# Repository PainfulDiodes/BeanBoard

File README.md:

# BeanBoard

QWERTY Keyboard, simple LCD display and GPIO for [BeanZee](https://github.com/PainfulDiodes/BeanZee)

# Design

## Keyboard  
Aiming for the simplest possible design, using a simple matrix of switches. 

Diodes are used with each switch to prevent [ghosting](https://en.wikipedia.org/wiki/Key_rollover#Key_jamming_and_ghosting).  

The circuit expects the CPU to send a "strobe" to a keyboard output port. A latch is used to capture the strobe - so that the state persists after the CPU has stopped outputting to the port. This strobe should have only one bit set high. This is the "live" row.

Then the CPU will read from a keyboard input port to sense which columns are high - columns will be activated by switches being pressed. A buffer is used to gate the columns onto the data bus.

The CPU will loop back and successively set each strobe bit high. Having gone through each bit and then read back the columns, we will have 64 bits of data (8x8) representing which keys are being pressed.

The 8 electronic rows are arranged as 4 physical rows, pairing electronic rows consecutively: 0+1, 2+3, 4+5, 6+7

## LCD
The [Hitachi HD44780 LCD controller](https://en.wikipedia.org/wiki/Hitachi_HD44780_LCD_controller) has been around since the 1980's and is still popular to control character-based LCD displays:  
* [HD44780 datasheet](https://cdn-shop.adafruit.com/datasheets/HD44780.pdf)   
* [Adafruit Standard LCD 20x4](https://www.adafruit.com/product/198)  

A parallel interface makes it CPU bus friendly - with 8 data bits, enable, R/W and register select inputs.

## GPIO

Repeating the keyboard logic allows for 8 general purpose binary outputs and inputs which can be used for experimentation.

## Port address decoding

A 3 to 8 decoder has been used to select pairs of ports. A0 is then used to chose between ports in a pair. The BeanZee board has the logic to separate ports based on A0, and there's a similar arrangement here for LCD. The keyboard ignores A0.

KBD_PORT equ 2 ; or 3  
LCD_CTRL equ 4 ; LCD control port  
LCD_DATA equ 5 ; LCD data port  
GPIO equ 6 ; or 7  

## Z80 bus

The BeanZee Z80 bus is extended on a BeanBoard connector to allow for expansion. Note that the MREQ_enable jumper is also extended to allow the memory select logic to be changed.

## Schematic
[BeanBoard Schematic](/kicad/BeanBoard.pdf)

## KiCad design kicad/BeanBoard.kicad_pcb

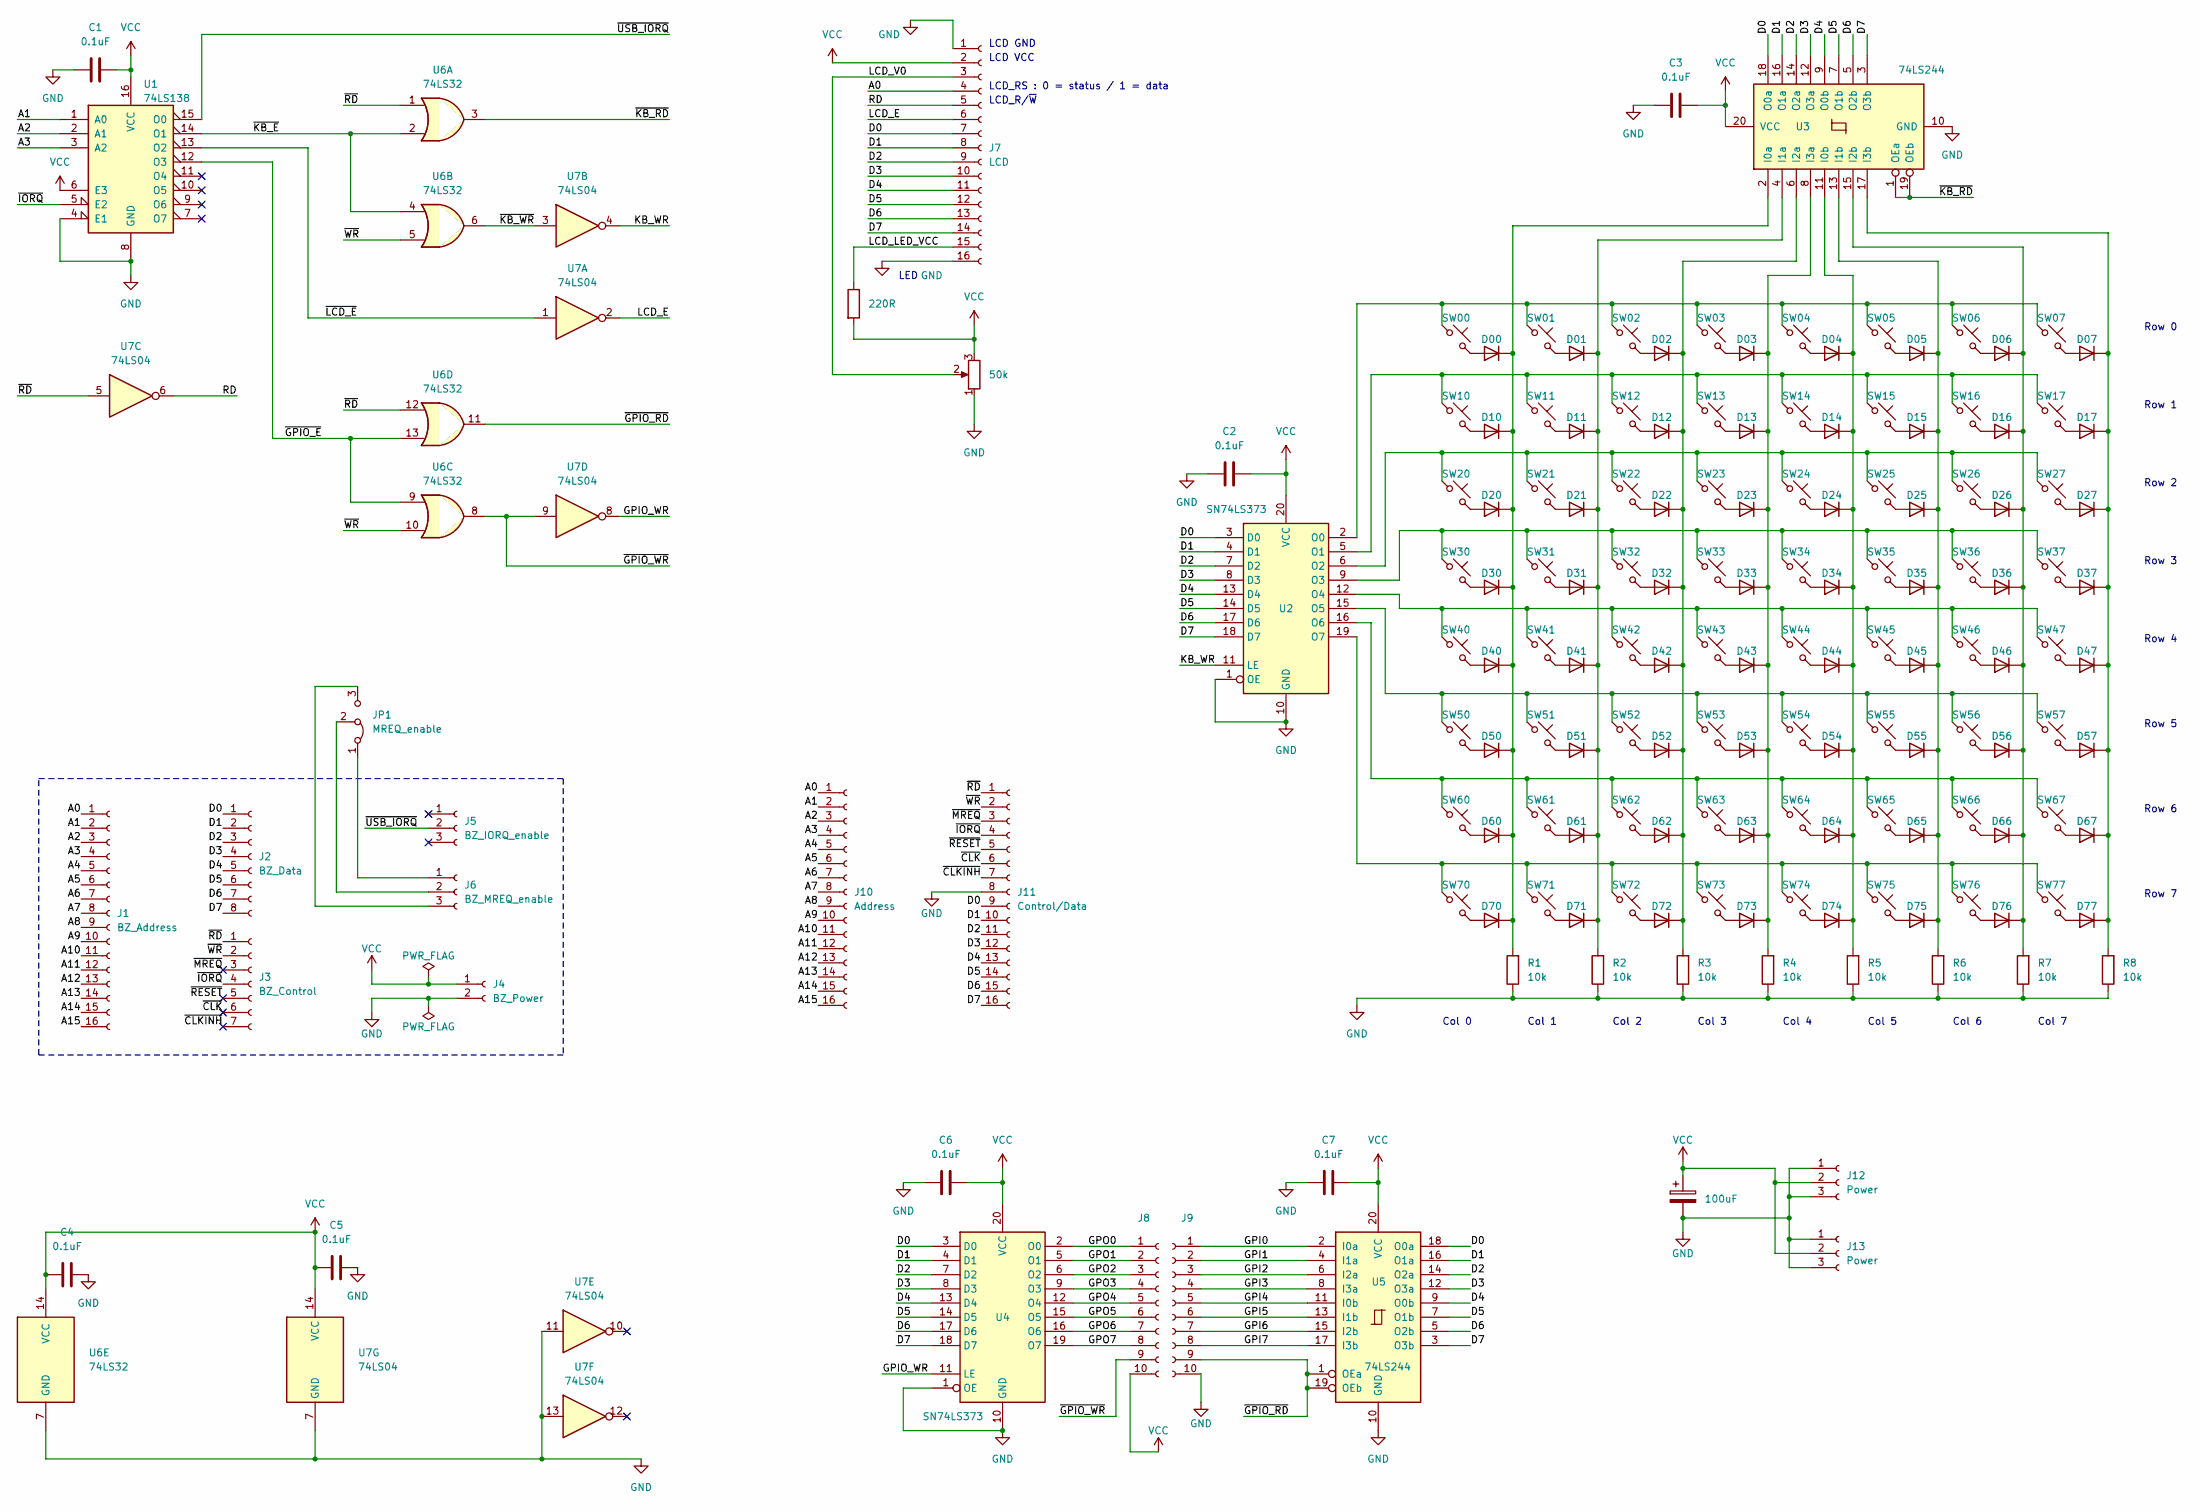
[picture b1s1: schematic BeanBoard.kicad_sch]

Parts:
C1, C2, C3, C4, C5, C6, C7: 0.1uF; C_Disc_D5.0mm_W2.5mm_P2.50mm
C8: 100uF; CP_Radial_D5.0mm_P2.00mm
D00, D01, D02, D03, D04, D05, D06, D07, D10, D11, D12, D13, D14, D15, D16, D17, D20, D21, D22, D23, D24, D25, D26, D27, D30, D31, D32, D33, D34, D35, D36, D37, D40, D41, D42, D43, D44, D45, D46, D47, D50, D51, D52, D53, D54, D55, D56, D57, D60, D61, D62, D63, D64, D65, D66, D67, D70, D71, D72, D73, D74, D75, D76, D77: 1N4148; D_DO-35_SOD27_P7.62mm_Horizontal
J1: BZ_Address; PinSocket_1x16_P2.54mm_Vertical
J2: BZ_Data; PinSocket_1x08_P2.54mm_Vertical
J3: BZ_Control; PinSocket_1x07_P2.54mm_Vertical
J4: BZ_Power; PinSocket_1x02_P2.54mm_Vertical
J5: BZ_IORQ_enable; PinSocket_1x03_P2.54mm_Vertical_alt
J6: BZ_MREQ_enable; PinSocket_1x03_P2.54mm_Vertical_alt
J7: LCD; PinSocket_1x16_P2.54mm_Vertical
J8: GPO; PinSocket_1x10_P2.54mm_Vertical
J9: GPI; PinSocket_1x10_P2.54mm_Vertical
J10: Address; PinSocket_1x16_P2.54mm_Vertical
J11: Control/Data; PinSocket_1x16_P2.54mm_Vertical
J12, J13: Power; PinSocket_1x03_P2.54mm_Vertical
JP1: MREQ_enable; PinSocket_1x03_P2.54mm_Vertical_alt
R1, R2, R3, R4, R5, R6, R7, R8: 10k; R_Axial_DIN0204_L3.6mm_D1.6mm_P7.62mm_Horizontal
R9: 220R; R_Axial_DIN0204_L3.6mm_D1.6mm_P7.62mm_Horizontal
RV1: 50k; Pot_THD_vertical_1x03_P2.54mm
SW00, SW01, SW02, SW03, SW04, SW05, SW06, SW07, SW10, SW11, SW12, SW13, SW14, SW15, SW16, SW17, SW20, SW21, SW22, SW23, SW24, SW25, SW26, SW27, SW30, SW31, SW32, SW33, SW34, SW35, SW36, SW37, SW40, SW41, SW42, SW43, SW44, SW45, SW46, SW47, SW50, SW51, SW52, SW53, SW54, SW55, SW56, SW57, SW60, SW61, SW62, SW63, SW64, SW65, SW66, SW67, SW70, SW71, SW72, SW73, SW74, SW75, SW76, SW77: SW_Push_45deg; SW_Cherry_MX_1.00u_PCB
U1: 74LS138; DIP-16_W7.62mm_Socket
U2, U4: SN74LS373; DIP-20_W7.62mm_Socket
U3, U5: 74LS244; DIP-20_W7.62mm_Socket
U6: 74LS32; DIP-14_W7.62mm_Socket
U7: 74LS04; DIP-14_W7.62mm_Socket

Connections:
/A0: J1.1, J7.4, J10.1
/A1: J1.2, J10.2, U1.1 (A0)
/A2: J1.3, J10.3, U1.2 (A1)
/A3: J1.4, J10.4, U1.3 (A2)
/A4: J1.5, J10.5
/A5: J1.6, J10.6
/A6: J1.7, J10.7
/A7: J1.8, J10.8
/A8: J1.9, J10.9
/A9: J1.10, J10.10
/A10: J1.11, J10.11
/A11: J1.12, J10.12
/A12: J1.13, J10.13
/A13: J1.14, J10.14
/A14: J1.15, J10.15
/A15: J1.16, J10.16
/D0: J2.1, J7.7, J11.9, U2.3 (D0), U3.18 (O0a), U4.3 (D0), U5.18 (O0a)
/D1: J2.2, J7.8, J11.10, U2.4 (D1), U3.16 (O1a), U4.4 (D1), U5.16 (O1a)
/D2: J2.3, J7.9, J11.11, U2.7 (D2), U3.14 (O2a), U4.7 (D2), U5.14 (O2a)
/D3: J2.4, J7.10, J11.12, U2.8 (D3), U3.12 (O3a), U4.8 (D3), U5.12 (O3a)
/D4: J2.5, J7.11, J11.13, U2.13 (D4), U3.9 (O0b), U4.13 (D4), U5.9 (O0b)
/D5: J2.6, J7.12, J11.14, U2.14 (D5), U3.7 (O1b), U4.14 (D5), U5.7 (O1b)
/D6: J2.7, J7.13, J11.15, U2.17 (D6), U3.5 (O2b), U4.17 (D6), U5.5 (O2b)
/D7: J2.8, J7.14, J11.16, U2.18 (D7), U3.3 (O3b), U4.18 (D7), U5.3 (O3b)
/GPI0: J9.1, U5.2 (I0a)
/GPI1: J9.2, U5.4 (I1a)
/GPI2: J9.3, U5.6 (I2a)
/GPI3: J9.4, U5.8 (I3a)
/GPI4: J9.5, U5.11 (I0b)
/GPI5: J9.6, U5.13 (I1b)
/GPI6: J9.7, U5.15 (I2b)
/GPI7: J9.8, U5.17 (I3b)
/GPIO_WR: U4.11 (LE), U7.8
/GPO0: J8.1, U4.2 (O0)
/GPO1: J8.2, U4.5 (O1)
/GPO2: J8.3, U4.6 (O2)
/GPO3: J8.4, U4.9 (O3)
/GPO4: J8.5, U4.12 (O4)
/GPO5: J8.6, U4.15 (O5)
/GPO6: J8.7, U4.16 (O6)
/GPO7: J8.8, U4.19 (O7)
/KB_WR: U2.11 (LE), U7.4
/LCD_E: J7.6, U7.2
/LCD_LED_VCC: J7.15, R9.1
/LCD_V0: J7.3, RV1.2
/RD: J7.5, U7.6
/~CLKINH: J3.7, J11.7
/~CLK: J3.6, J11.6
/~GPIO_E: U1.12 (O3), U6.9, U6.13
/~GPIO_RD: J9.9, U5.1 (OEa), U5.19 (OEb), U6.11
/~GPIO_WR: J8.9, U6.8, U7.9
/~IORQ: J3.4, J11.4, U1.5 (E2)
/~KB_E: U1.14 (O1), U6.2, U6.4
/~KB_RD: U3.1 (OEa), U3.19 (OEb), U6.3
/~KB_WR: U6.6, U7.3
/~LCD_E: U1.13 (O2), U7.1
/~MREQ: J3.3, J11.3
/~RD: J3.1, J11.1, U6.1, U6.12, U7.5
/~RESET: J3.5, J11.5
/~USB_IORQ: J5.2, U1.15 (O0)
/~WR: J3.2, J11.2, U6.5, U6.10
GND: C1.1, C2.1, C3.1, C4.2, C5.2, C6.1, C7.1, C8.2, J4.2, J7.1, J7.16, J9.10, J11.8, J12.1, J12.3, J13.1, J13.3, R1.1, R2.1, R3.1, R4.1, R5.1, R6.1, R7.1, R8.1, RV1.1, U1.4 (E1), U1.8 (GND), U2.1 (OE), U2.10 (GND), U3.10 (GND), U4.1 (OE), U4.10 (GND), U5.10 (GND), U6.7 (GND), U7.7 (GND), U7.11, U7.13
unnamed: D00.2 (A), SW00.2
unnamed: D00.1 (K), D10.1 (K), D20.1 (K), D30.1 (K), D40.1 (K), D50.1 (K), D60.1 (K), D70.1 (K), R1.2, U3.2 (I0a)
unnamed: D01.2 (A), SW01.2
unnamed: D01.1 (K), D11.1 (K), D21.1 (K), D31.1 (K), D41.1 (K), D51.1 (K), D61.1 (K), D71.1 (K), R2.2, U3.4 (I1a)
unnamed: D02.2 (A), SW02.2
unnamed: D02.1 (K), D12.1 (K), D22.1 (K), D32.1 (K), D42.1 (K), D52.1 (K), D62.1 (K), D72.1 (K), R3.2, U3.6 (I2a)
unnamed: D03.2 (A), SW03.2
unnamed: D03.1 (K), D13.1 (K), D23.1 (K), D33.1 (K), D43.1 (K), D53.1 (K), D63.1 (K), D73.1 (K), R4.2, U3.8 (I3a)
unnamed: D04.2 (A), SW04.2
unnamed: D04.1 (K), D14.1 (K), D24.1 (K), D34.1 (K), D44.1 (K), D54.1 (K), D64.1 (K), D74.1 (K), R5.2, U3.11 (I0b)
unnamed: D05.2 (A), SW05.2
unnamed: D05.1 (K), D15.1 (K), D25.1 (K), D35.1 (K), D45.1 (K), D55.1 (K), D65.1 (K), D75.1 (K), R6.2, U3.13 (I1b)
unnamed: D06.2 (A), SW06.2
unnamed: D06.1 (K), D16.1 (K), D26.1 (K), D36.1 (K), D46.1 (K), D56.1 (K), D66.1 (K), D76.1 (K), R7.2, U3.15 (I2b)
unnamed: D07.2 (A), SW07.2
unnamed: D07.1 (K), D17.1 (K), D27.1 (K), D37.1 (K), D47.1 (K), D57.1 (K), D67.1 (K), D77.1 (K), R8.2, U3.17 (I3b)
unnamed: D10.2 (A), SW10.2
unnamed: D11.2 (A), SW11.2
unnamed: D12.2 (A), SW12.2
unnamed: D13.2 (A), SW13.2
unnamed: D14.2 (A), SW14.2
unnamed: D15.2 (A), SW15.2
unnamed: D16.2 (A), SW16.2
unnamed: D17.2 (A), SW17.2
unnamed: D20.2 (A), SW20.2
unnamed: D21.2 (A), SW21.2
unnamed: D22.2 (A), SW22.2
unnamed: D23.2 (A), SW23.2
unnamed: D24.2 (A), SW24.2
unnamed: D25.2 (A), SW25.2
unnamed: D26.2 (A), SW26.2
unnamed: D27.2 (A), SW27.2
unnamed: D30.2 (A), SW30.2
unnamed: D31.2 (A), SW31.2
unnamed: D32.2 (A), SW32.2
unnamed: D33.2 (A), SW33.2
unnamed: D34.2 (A), SW34.2
unnamed: D35.2 (A), SW35.2
unnamed: D36.2 (A), SW36.2
unnamed: D37.2 (A), SW37.2
unnamed: D40.2 (A), SW40.2
unnamed: D41.2 (A), SW41.2
unnamed: D42.2 (A), SW42.2
unnamed: D43.2 (A), SW43.2
unnamed: D44.2 (A), SW44.2
unnamed: D45.2 (A), SW45.2
unnamed: D46.2 (A), SW46.2
unnamed: D47.2 (A), SW47.2
unnamed: D50.2 (A), SW50.2
unnamed: D51.2 (A), SW51.2
unnamed: D52.2 (A), SW52.2
unnamed: D53.2 (A), SW53.2
unnamed: D54.2 (A), SW54.2
unnamed: D55.2 (A), SW55.2
unnamed: D56.2 (A), SW56.2
unnamed: D57.2 (A), SW57.2
unnamed: D60.2 (A), SW60.2
unnamed: D61.2 (A), SW61.2
unnamed: D62.2 (A), SW62.2
unnamed: D63.2 (A), SW63.2
unnamed: D64.2 (A), SW64.2
unnamed: D65.2 (A), SW65.2
unnamed: D66.2 (A), SW66.2
unnamed: D67.2 (A), SW67.2
unnamed: D70.2 (A), SW70.2
unnamed: D71.2 (A), SW71.2
unnamed: D72.2 (A), SW72.2
unnamed: D73.2 (A), SW73.2
unnamed: D74.2 (A), SW74.2
unnamed: D75.2 (A), SW75.2
unnamed: D76.2 (A), SW76.2
unnamed: D77.2 (A), SW77.2
unnamed: J6.1, JP1.1 (A)
unnamed: J6.2, JP1.2 (C)
unnamed: J6.3, JP1.3 (B)
unnamed: SW00.1, SW01.1, SW02.1, SW03.1, SW04.1, SW05.1, SW06.1, SW07.1, U2.2 (O0)
unnamed: SW10.1, SW11.1, SW12.1, SW13.1, SW14.1, SW15.1, SW16.1, SW17.1, U2.5 (O1)
unnamed: SW20.1, SW21.1, SW22.1, SW23.1, SW24.1, SW25.1, SW26.1, SW27.1, U2.6 (O2)
unnamed: SW30.1, SW31.1, SW32.1, SW33.1, SW34.1, SW35.1, SW36.1, SW37.1, U2.9 (O3)
unnamed: SW40.1, SW41.1, SW42.1, SW43.1, SW44.1, SW45.1, SW46.1, SW47.1, U2.12 (O4)
unnamed: SW50.1, SW51.1, SW52.1, SW53.1, SW54.1, SW55.1, SW56.1, SW57.1, U2.15 (O5)
unnamed: SW60.1, SW61.1, SW62.1, SW63.1, SW64.1, SW65.1, SW66.1, SW67.1, U2.16 (O6)
unnamed: SW70.1, SW71.1, SW72.1, SW73.1, SW74.1, SW75.1, SW76.1, SW77.1, U2.19 (O7)
VCC: C1.2, C2.2, C3.2, C4.1, C5.1, C6.2, C7.2, C8.1, J4.1, J7.2, J8.10, J12.2, J13.2, R9.2, RV1.3, U1.6 (E3), U1.16 (VCC), U2.20 (VCC), U3.20 (VCC), U4.20 (VCC), U5.20 (VCC), U6.14 (VCC), U7.14 (VCC)

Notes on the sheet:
Row 0
Col 3
LED
LCD_R/~{W}
LCD_RS : 0 = status / 1 = data
Col 1
Col 6
Row 7
Row 1
LCD GND
Row 5
Col 5
LCD VCC
Col 0
Row 6
Col 2
Row 3
Col 4
Col 7
Row 4
Row 2

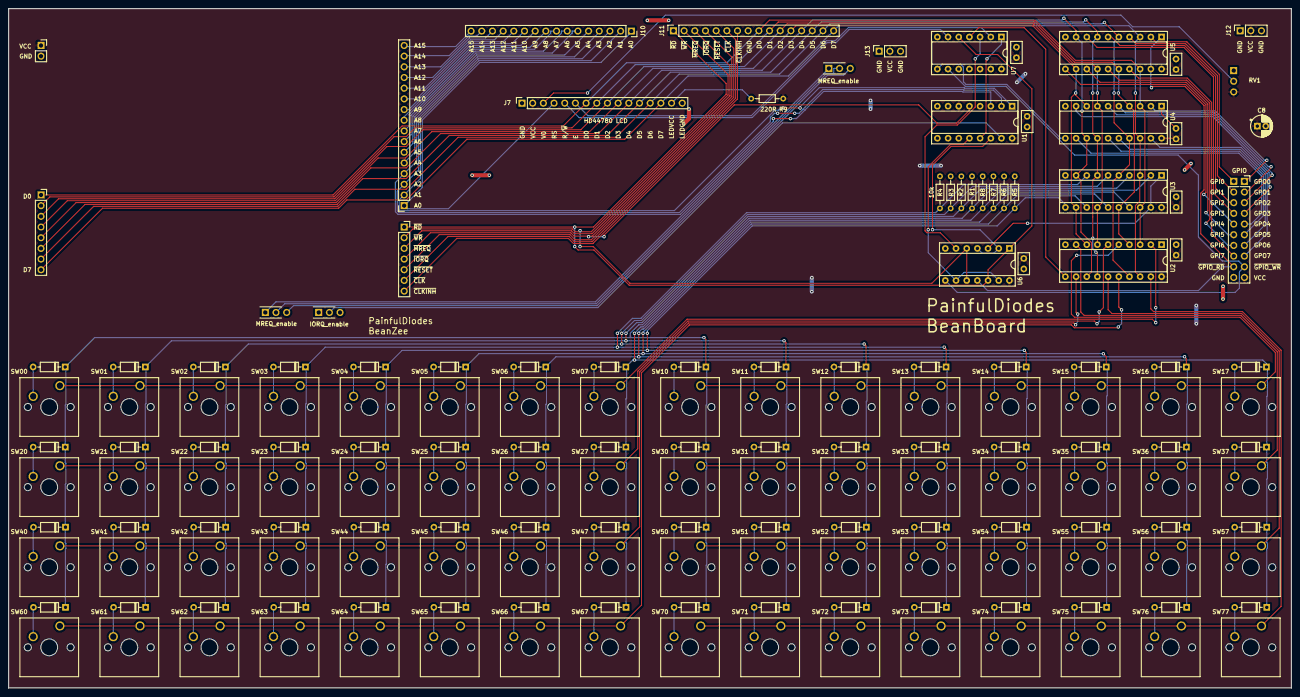
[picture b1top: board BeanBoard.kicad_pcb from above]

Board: 2 copper layers, 305.1 x 161.5 mm, 167 parts (0 on the bottom side), 146 nets.

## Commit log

2025-02-01 kicad
2025-02-02 First complete pass
2025-03-22 Prototyping update
2025-03-23 Create fp-lib-table
2025-03-23 Create sym-lib-table
2025-03-25 Update BeanBoard.kicad_pcb
    Reset
2025-03-29 gerbers
2025-03-29 pcb visualisation
2025-03-29 Added silkscreen annotations
2025-04-07 Move out schematic and PCB
2025-05-04 reinstate schematics and pcb layout
2025-05-08 Update fp-lib-table
2025-05-20 pcb plot
2025-05-21 readme and photos
2025-05-21 Prototype
2025-06-03 Remove port decoding options
2025-06-03 images
